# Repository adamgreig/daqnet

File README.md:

# DAQnet

Experiment into FPGAs for distributed data acquisition.

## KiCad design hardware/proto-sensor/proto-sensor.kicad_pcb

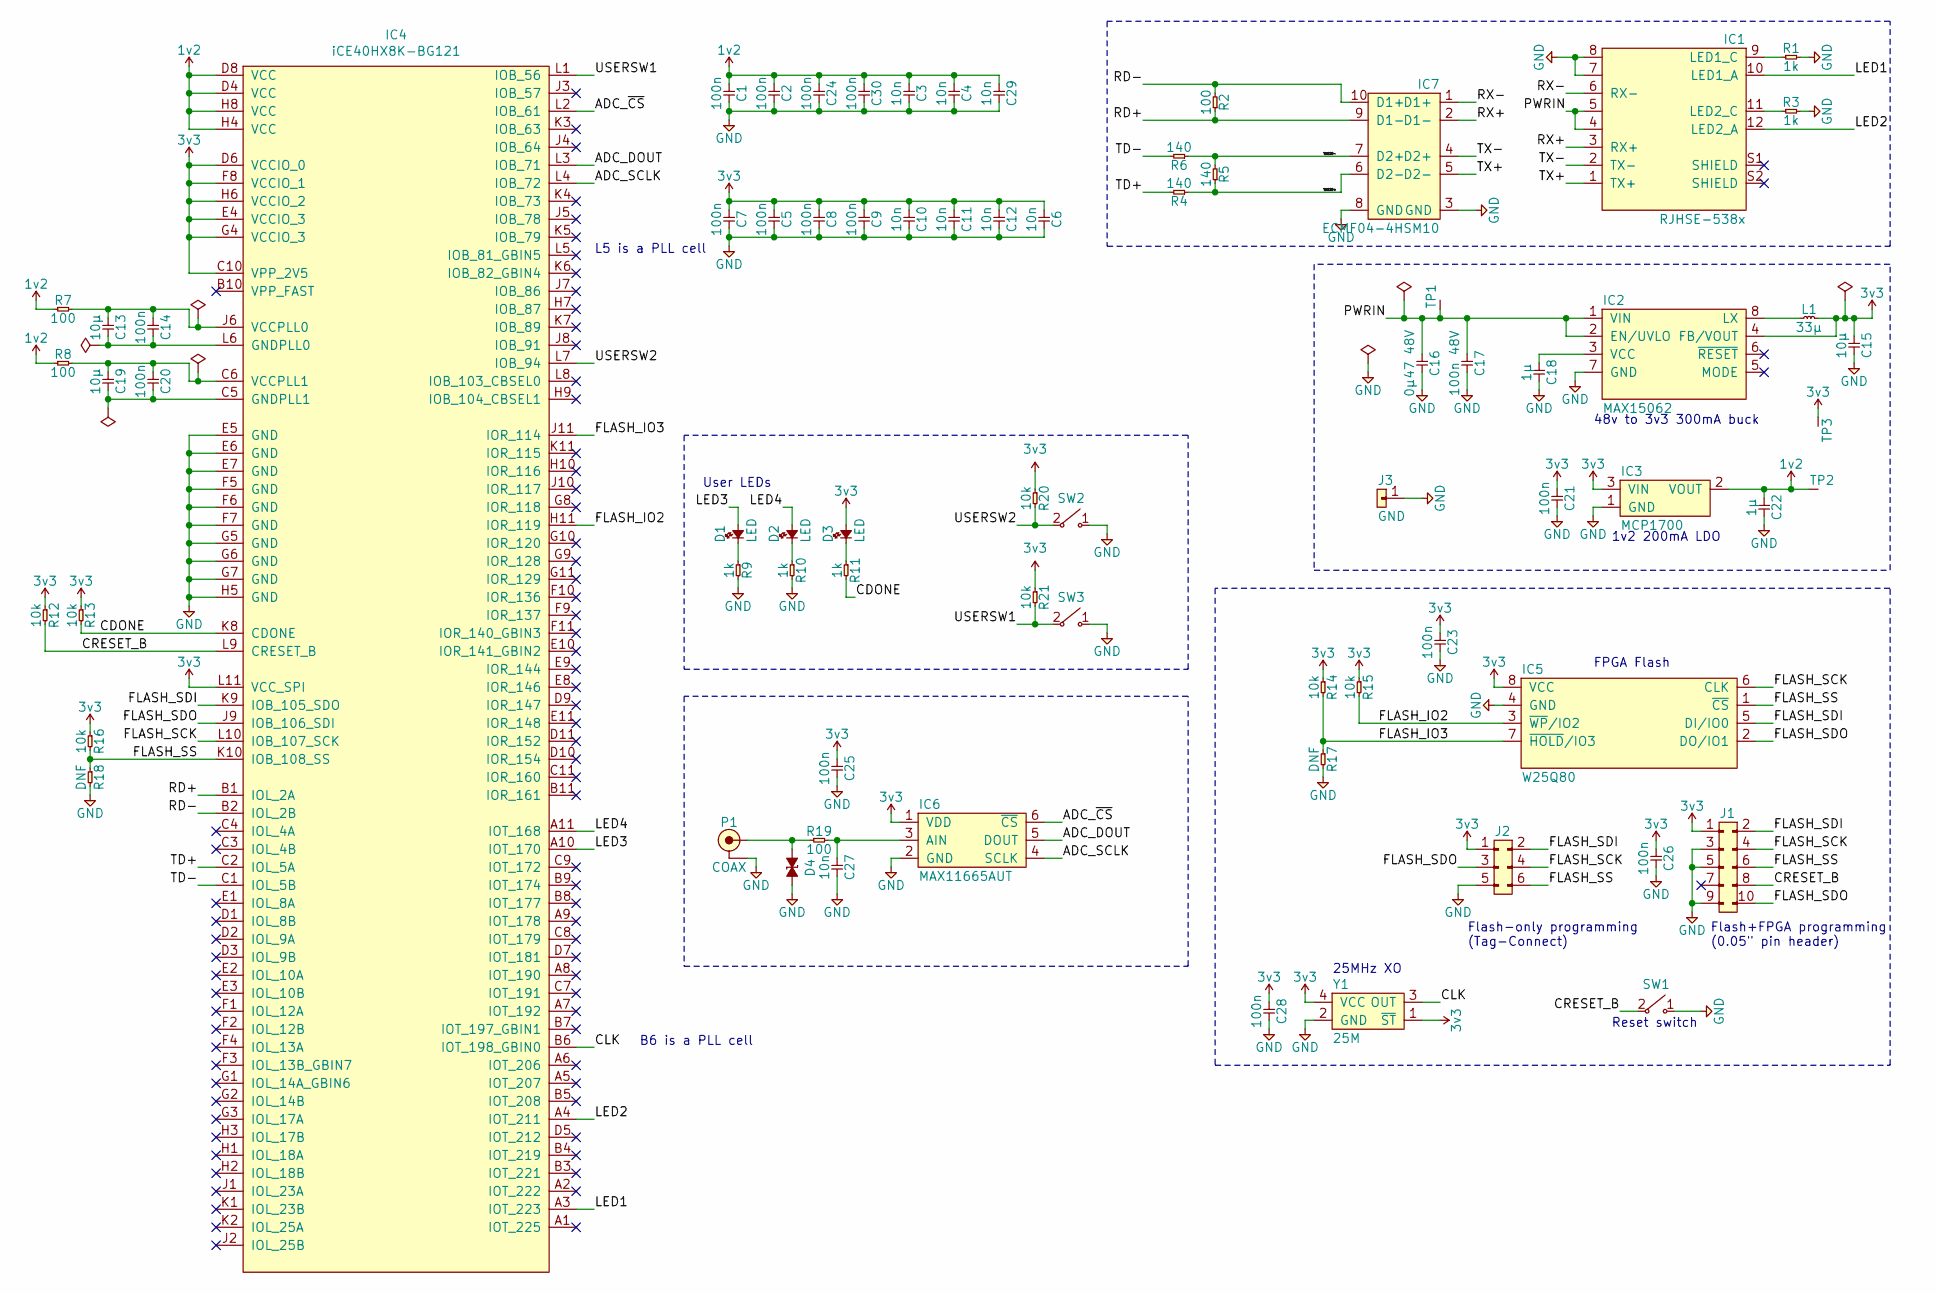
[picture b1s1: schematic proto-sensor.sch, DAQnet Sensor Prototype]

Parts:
C1, C2, C5, C7, C8, C9, C14, C20, C21, C23, C24, C25, C26, C28, C30: 100n; 0402; Voltage Rating 16; Farnell 2810260
C3, C4, C6, C10, C11, C12, C27, C29: 10n; 0402; Voltage Rating 50; Farnell 2470416
C13, C15, C19: 10µ; 0603; Voltage Rating 6.3; Farnell 2611921
C16: 0µ47 48V; 0603; Voltage Rating 50; Farnell 2211183
C17: 100n 48V; 0603; Voltage Rating 50; Farnell 431989
C18, C22: 1µ; 0402; Voltage Rating 10; Farnell 1458896
D1, D2: LED; 0603-LED; Farnell 2290328
D3: LED; 0603-LED; Farnell 2290329
D4: ESD_DIODE; 0402; Farnell 2368169
IC1: RJHSE-538x; RJHSE-538X; Farnell 1462758
IC2: MAX15062; TDFN-8; Farnell 2516650
IC3: MCP1700; SOT-23; Farnell 1851940
IC4: iCE40HX8K-BG121; Lattice-BG121; DigiKey 220-2148-ND
IC5: W25Q80; UFDFN-8; DigiKey W25Q80DVUXIECT-ND
IC6: MAX11665AUT; SOT-23-6; Farnell 2513633
IC7: ECMF04-4HSM10; uQFN-10L; Farnell 2462664
J1: FTSH-105-01-F-D-K; Farnell 2856426
J2: TC2030-NL
J3: GND; SIL-254P-01
L1: 33µ; LPS4018; Farnell 2408110
P1: COAX; BNC_PCB_RA_5-1634556-0; Farnell 1248952
R1, R3, R9, R10, R11: 1k; 0402; Voltage Rating 50; Farnell 2331474
R2, R7, R8, R19: 100; 0402; Voltage Rating 50; Farnell 9239111
R4, R5, R6: 140; 0402; Voltage Rating 50; Farnell 2302541
R12, R13, R14, R15, R16, R20, R21: 10k; 0402; Voltage Rating 50; Farnell 2302739
R17, R18: DNF; 0402
SW1, SW2, SW3: KSR232G; Farnell 2845744
TP1, TP2, TP3: TESTPAD
Y1: 25M; XTAL-25x20; Farnell 2849479

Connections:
1v2: C1.1, C2.1, C3.1, C4.1, C22.1, C24.1, C29.1, C30.1, IC3.2 (VOUT), IC4.D4 (VCC), IC4.D8 (VCC), IC4.H4 (VCC), IC4.H8 (VCC), R7.1, R8.1, TP2.1
3v3: C5.1, C6.1, C7.1, C8.1, C9.1, C10.1, C11.1, C12.1, C15.1, C21.1, C23.1, C25.1, C26.1, C28.1, D3.2, IC2.4 (FB/VOUT), IC3.3 (VIN), IC4.C10 (VPP_2V5), IC4.D6 (VCCIO_0), IC4.E4 (VCCIO_3), IC4.F8 (VCCIO_1), IC4.G4 (VCCIO_3), IC4.H6 (VCCIO_2), IC4.L11 (VCC_SPI), IC5.8 (VCC), IC6.1 (VDD), J1.1, J2.1, L1.2, R12.1, R13.1, R14.1, R15.1, R16.1, R20.1, R21.1, TP3.1, Y1.1 (~ST), Y1.4 (VCC)
/ADC_DOUT: IC4.L3 (IOB_71), IC6.5 (DOUT)
/ADC_SCLK: IC4.L4 (IOB_72), IC6.4 (SCLK)
/ADC_~CS: IC4.L2 (IOB_61), IC6.6 (~CS)
/CDONE: IC4.K8 (CDONE), R11.2, R13.2
/CLK: IC4.B6 (IOT_198_GBIN0), Y1.3 (OUT)
/CRESET_B: IC4.L9 (CRESET_B), J1.8, R12.2, SW1.2
/FLASH_IO2: IC4.H11 (IOR_119), IC5.3 (~WP~/IO2), R15.2
/FLASH_IO3: IC4.J11 (IOR_114), IC5.7 (~HOLD~/IO3), R14.2, R17.1
/FLASH_SCK: IC4.L10 (IOB_107_SCK), IC5.6 (CLK), J1.4, J2.4
/FLASH_SDI: IC4.K9 (IOB_105_SDO), IC5.5 (DI/IO0), J1.2, J2.2
/FLASH_SDO: IC4.J9 (IOB_106_SDI), IC5.2 (DO/IO1), J1.10, J2.3
/FLASH_SS: IC4.K10 (IOB_108_SS), IC5.1 (~CS), J1.6, J2.6, R16.2, R18.1
/LED1: IC1.10 (LED1_A), IC4.A3 (IOT_223)
/LED2: IC1.12 (LED2_A), IC4.A4 (IOT_211)
/LED3: D1.2, IC4.A10 (IOT_170)
/LED4: D2.2, IC4.A11 (IOT_168)
/PWRIN: C16.1, C17.1, IC1.4, IC1.5, IC2.1 (VIN), IC2.2 (EN/UVLO), TP1.1
/RD+: IC4.B1 (IOL_2A), IC7.9 (D1-), R2.1
/RD-: IC4.B2 (IOL_2B), IC7.10 (D1+), R2.2
/RX+: IC1.3 (RX+), IC7.2 (D1-)
/RX-: IC1.6 (RX-), IC7.1 (D1+)
/TD+: IC4.C2 (IOL_5A), R4.2
/TD-: IC4.C1 (IOL_5B), R6.2
/TDESD+: IC7.6 (D2-), R4.1, R5.1
/TDESD-: IC7.7 (D2+), R5.2, R6.1
/TX+: IC1.1 (TX+), IC7.5 (D2-)
/TX-: IC1.2 (TX-), IC7.4 (D2+)
/USERSW1: IC4.L1 (IOB_56), R21.2, SW3.2
/USERSW2: IC4.L7 (IOB_94), R20.2, SW2.2
GND: C1.2, C2.2, C3.2, C4.2, C5.2, C6.2, C7.2, C8.2, C9.2, C10.2, C11.2, C12.2, C15.2, C16.2, C17.2, C18.2, C21.2, C22.2, C23.2, C24.2, C25.2, C26.2, C27.2, C28.2, C29.2, C30.2, D4.2, IC1.7, IC1.8, IC2.7 (GND), IC3.1 (GND), IC4.E5 (GND), IC4.E6 (GND), IC4.E7 (GND), IC4.F5 (GND), IC4.F6 (GND), IC4.F7 (GND), IC4.G5 (GND), IC4.G6 (GND), IC4.G7 (GND), IC4.H5 (GND), IC5.4 (GND), IC6.2 (GND), IC7.3 (GND), IC7.8 (GND), J1.3, J1.5, J1.9, J2.5, J3.1, P1.2 (GND), R1.2, R3.2, R9.2, R10.2, R17.2, R18.2, SW1.1, SW2.1, SW3.1, Y1.2 (GND)
unnamed: C13.1, C14.1, IC4.J6 (VCCPLL0), R7.2
unnamed: C13.2, C14.2, IC4.L6 (GNDPLL0)
unnamed: C18.1, IC2.3 (VCC)
unnamed: C19.1, C20.1, IC4.C6 (VCCPLL1), R8.2
unnamed: C19.2, C20.2, IC4.C5 (GNDPLL1)
unnamed: C27.1, IC6.3 (AIN), R19.2
unnamed: D1.1, R9.1
unnamed: D2.1, R10.1
unnamed: D3.1, R11.1
unnamed: D4.1, P1.1 (RF), R19.1
unnamed: IC1.9 (LED1_C), R1.1
unnamed: IC1.11 (LED2_C), R3.1
unnamed: IC2.8 (LX), L1.1

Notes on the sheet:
Flash-only programming (Tag-Connect)
Flash+FPGA programming (0.05" pin header)
FPGA Flash
48v to 3v3 300mA buck
25MHz XO
Reset switch
User LEDs
1v2 200mA LDO
L5 is a PLL cell
B6 is a PLL cell

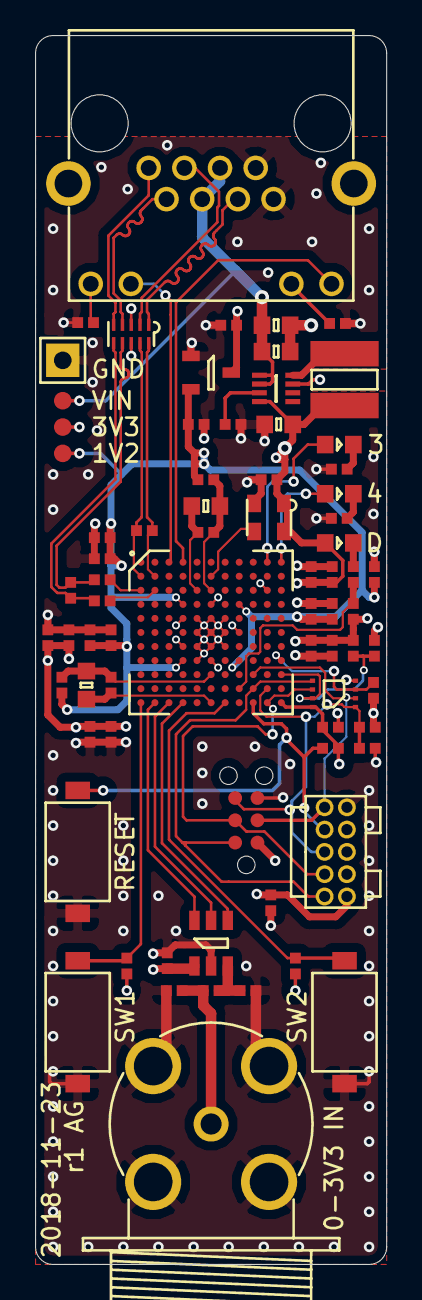
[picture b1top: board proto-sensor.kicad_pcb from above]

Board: 4 copper layers, 20.0 x 70.0 mm, 74 parts (0 on the bottom side), 45 nets.

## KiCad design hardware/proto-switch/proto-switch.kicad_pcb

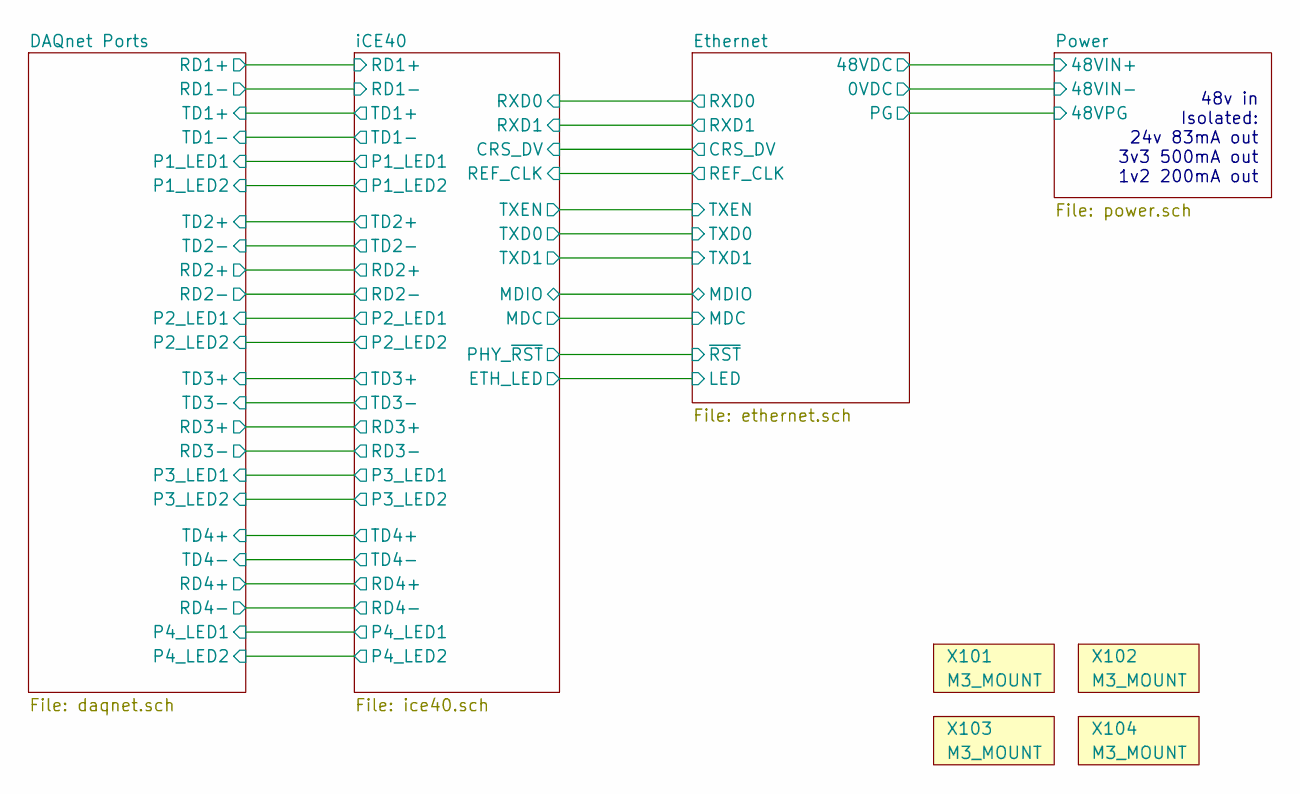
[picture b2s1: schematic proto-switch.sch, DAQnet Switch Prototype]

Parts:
X101, X102, X103, X104: M3_MOUNT

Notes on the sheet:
48v in Isolated: 24v 83mA out 3v3 500mA out 1v2 200mA out

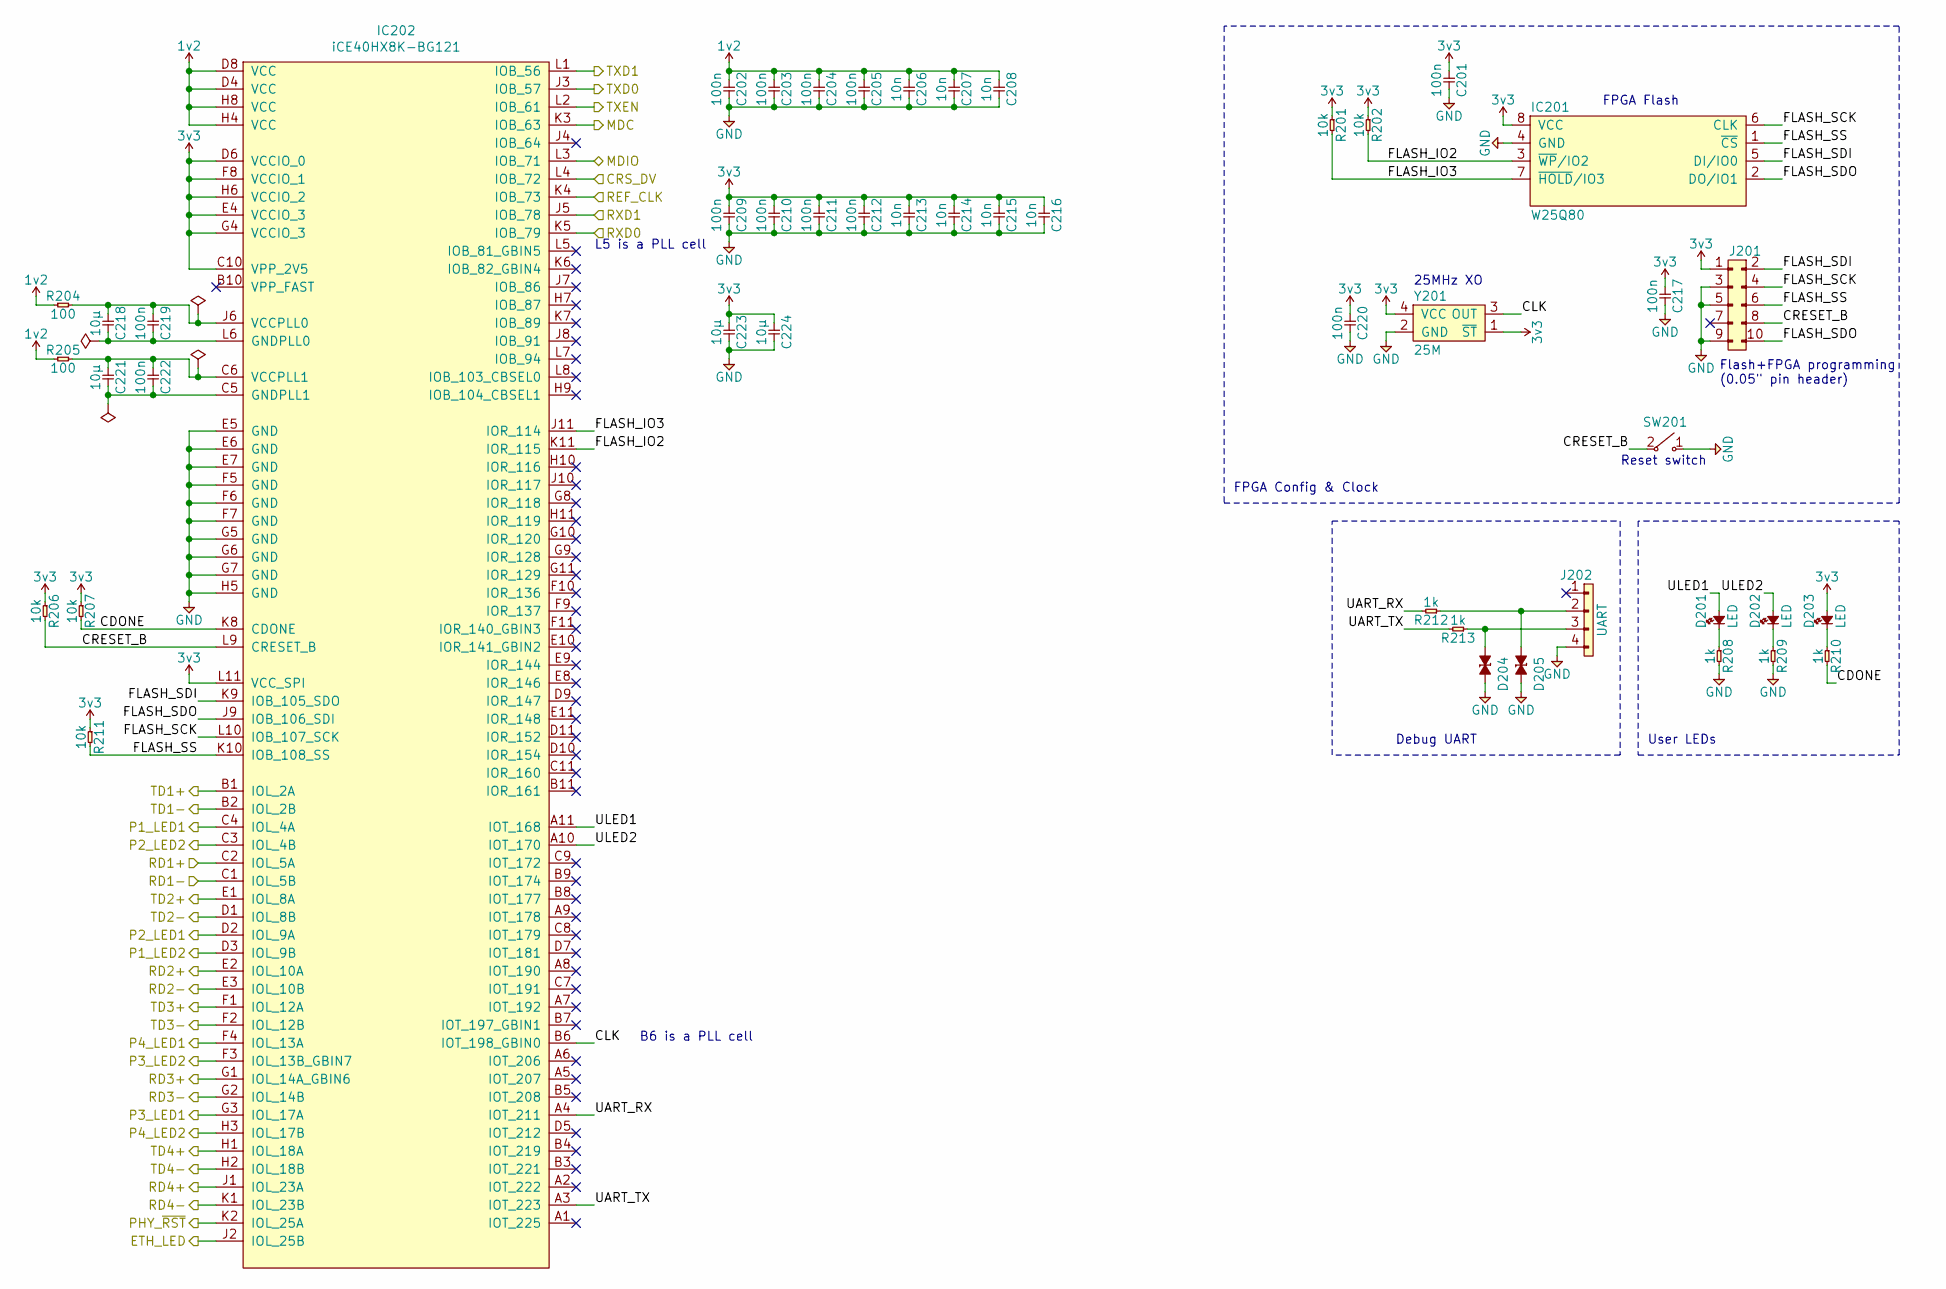
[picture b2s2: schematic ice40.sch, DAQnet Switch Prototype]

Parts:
C201, C202, C203, C204, C205, C209, C210, C211, C212, C217, C219, C220, C222: 100n; 0402; Voltage 16; Farnell 2810260
C206, C207, C208, C213, C214, C215, C216: 10n; 0402; Voltage 50; Farnell 2470416
C218, C221, C223, C224: 10µ; 0603; Voltage 6.3; Farnell 2611921
D201, D202: LED; 0603-LED; Farnell 2290328
D203: LED; 0603-LED; Farnell 2290329
D204, D205: ESD_DIODE; 0402; Farnell 2368169
IC201: W25Q80; UFDFN-8; DigiKey W25Q80DVUXIECT-ND
IC202: iCE40HX8K-BG121; Lattice-BG121; DigiKey 220-2148-ND
J201: FTSH-105-01-F-D-K; Farnell 2856426
J202: UART; SM04B-PASS
R201, R202, R206, R207, R211: 10k; 0402; Voltage 50; Farnell 2302739
R204, R205: 100; 0402; Voltage 50; Farnell 9239111
R208, R209, R210, R212, R213: 1k; 0402; Voltage 50; Farnell 2331474
SW201: KSR232G; Farnell 2845744
Y201: 25M; XTAL-25x20; Farnell 2849479

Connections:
1v2: C202.1, C203.1, C204.1, C205.1, C206.1, C207.1, C208.1, IC202.D4 (VCC), IC202.D8 (VCC), IC202.H4 (VCC), IC202.H8 (VCC), R204.1, R205.1; also elsewhere on the board
3v3: C201.1, C209.1, C210.1, C211.1, C212.1, C213.1, C214.1, C215.1, C216.1, C217.1, C220.1, C223.1, C224.1, D203.2, IC201.8 (VCC), IC202.C10 (VPP_2V5), IC202.D6 (VCCIO_0), IC202.E4 (VCCIO_3), IC202.F8 (VCCIO_1), IC202.G4 (VCCIO_3), IC202.H6 (VCCIO_2), IC202.L11 (VCC_SPI), J201.1, R201.1, R202.1, R206.1, R207.1, R211.1, Y201.1 (~ST), Y201.4 (VCC); also elsewhere on the board
/DAQnet Ports/P1_LED1: IC202.C4 (IOL_4A); also elsewhere on the board
/DAQnet Ports/P1_LED2: IC202.D3 (IOL_9B); also elsewhere on the board
/DAQnet Ports/P2_LED1: IC202.D2 (IOL_9A); also elsewhere on the board
/DAQnet Ports/P2_LED2: IC202.C3 (IOL_4B); also elsewhere on the board
/DAQnet Ports/P3_LED1: IC202.G3 (IOL_17A); also elsewhere on the board
/DAQnet Ports/P3_LED2: IC202.F3 (IOL_13B_GBIN7); also elsewhere on the board
/DAQnet Ports/P4_LED1: IC202.F4 (IOL_13A); also elsewhere on the board
/DAQnet Ports/P4_LED2: IC202.H3 (IOL_17B); also elsewhere on the board
/DAQnet Ports/RD1+: IC202.C2 (IOL_5A); also elsewhere on the board
/DAQnet Ports/RD1-: IC202.C1 (IOL_5B); also elsewhere on the board
/DAQnet Ports/RD2+: IC202.E2 (IOL_10A); also elsewhere on the board
/DAQnet Ports/RD2-: IC202.E3 (IOL_10B); also elsewhere on the board
/DAQnet Ports/RD3+: IC202.G1 (IOL_14A_GBIN6); also elsewhere on the board
/DAQnet Ports/RD3-: IC202.G2 (IOL_14B); also elsewhere on the board
/DAQnet Ports/RD4+: IC202.J1 (IOL_23A); also elsewhere on the board
/DAQnet Ports/RD4-: IC202.K1 (IOL_23B); also elsewhere on the board
/DAQnet Ports/TD1+: IC202.B1 (IOL_2A); also elsewhere on the board
/DAQnet Ports/TD1-: IC202.B2 (IOL_2B); also elsewhere on the board
/DAQnet Ports/TD2+: IC202.E1 (IOL_8A); also elsewhere on the board
/DAQnet Ports/TD2-: IC202.D1 (IOL_8B); also elsewhere on the board
/DAQnet Ports/TD3+: IC202.F1 (IOL_12A); also elsewhere on the board
/DAQnet Ports/TD3-: IC202.F2 (IOL_12B); also elsewhere on the board
/DAQnet Ports/TD4+: IC202.H1 (IOL_18A); also elsewhere on the board
/DAQnet Ports/TD4-: IC202.H2 (IOL_18B); also elsewhere on the board
/Ethernet/CRS_DV: IC202.L4 (IOB_72); also elsewhere on the board
/Ethernet/MDC: IC202.K3 (IOB_63); also elsewhere on the board
/Ethernet/MDIO: IC202.L3 (IOB_71); also elsewhere on the board
/Ethernet/REF_CLK: IC202.K4 (IOB_73); also elsewhere on the board
/Ethernet/RXD0: IC202.K5 (IOB_79); also elsewhere on the board
/Ethernet/RXD1: IC202.J5 (IOB_78); also elsewhere on the board
/Ethernet/TXD0: IC202.J3 (IOB_57); also elsewhere on the board
/Ethernet/TXD1: IC202.L1 (IOB_56); also elsewhere on the board
/Ethernet/TXEN: IC202.L2 (IOB_61); also elsewhere on the board
/iCE40/CDONE: IC202.K8 (CDONE), R207.2, R210.2
/iCE40/CLK: IC202.B6 (IOT_198_GBIN0), Y201.3 (OUT)
/iCE40/CRESET_B: IC202.L9 (CRESET_B), J201.8, R206.2, SW201.2
/iCE40/ETH_LED: IC202.J2 (IOL_25B); also elsewhere on the board
/iCE40/FLASH_IO2: IC201.3 (~WP~/IO2), IC202.K11 (IOR_115), R202.2
/iCE40/FLASH_IO3: IC201.7 (~HOLD~/IO3), IC202.J11 (IOR_114), R201.2
/iCE40/FLASH_SCK: IC201.6 (CLK), IC202.L10 (IOB_107_SCK), J201.4
/iCE40/FLASH_SDI: IC201.5 (DI/IO0), IC202.K9 (IOB_105_SDO), J201.2
/iCE40/FLASH_SDO: IC201.2 (DO/IO1), IC202.J9 (IOB_106_SDI), J201.10
/iCE40/FLASH_SS: IC201.1 (~CS), IC202.K10 (IOB_108_SS), J201.6, R211.2
/iCE40/PHY_~RST: IC202.K2 (IOL_25A); also elsewhere on the board
/iCE40/UART_RX: IC202.A4 (IOT_211), R212.2
/iCE40/UART_TX: IC202.A3 (IOT_223), R213.2
/iCE40/ULED1: D201.2, IC202.A11 (IOT_168)
/iCE40/ULED2: D202.2, IC202.A10 (IOT_170)
GND: C201.2, C202.2, C203.2, C204.2, C205.2, C206.2, C207.2, C208.2, C209.2, C210.2, C211.2, C212.2, C213.2, C214.2, C215.2, C216.2, C217.2, C220.2, C223.2, C224.2, D204.2, D205.2, IC201.4 (GND), IC202.E5 (GND), IC202.E6 (GND), IC202.E7 (GND), IC202.F5 (GND), IC202.F6 (GND), IC202.F7 (GND), IC202.G5 (GND), IC202.G6 (GND), IC202.G7 (GND), IC202.H5 (GND), J201.3, J201.5, J201.9, J202.4, R208.2, R209.2, SW201.1, Y201.2 (GND); also elsewhere on the board
unnamed: C218.1, C219.1, IC202.J6 (VCCPLL0), R204.2
unnamed: C218.2, C219.2, IC202.L6 (GNDPLL0)
unnamed: C221.1, C222.1, IC202.C6 (VCCPLL1), R205.2
unnamed: C221.2, C222.2, IC202.C5 (GNDPLL1)
unnamed: D201.1, R208.1
unnamed: D202.1, R209.1
unnamed: D203.1, R210.1
unnamed: D204.1, J202.3, R213.1
unnamed: D205.1, J202.2, R212.1

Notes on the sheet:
User LEDs
L5 is a PLL cell
B6 is a PLL cell
Flash+FPGA programming (0.05" pin header)
FPGA Flash
25MHz XO
Reset switch
Debug UART
FPGA Config & Clock

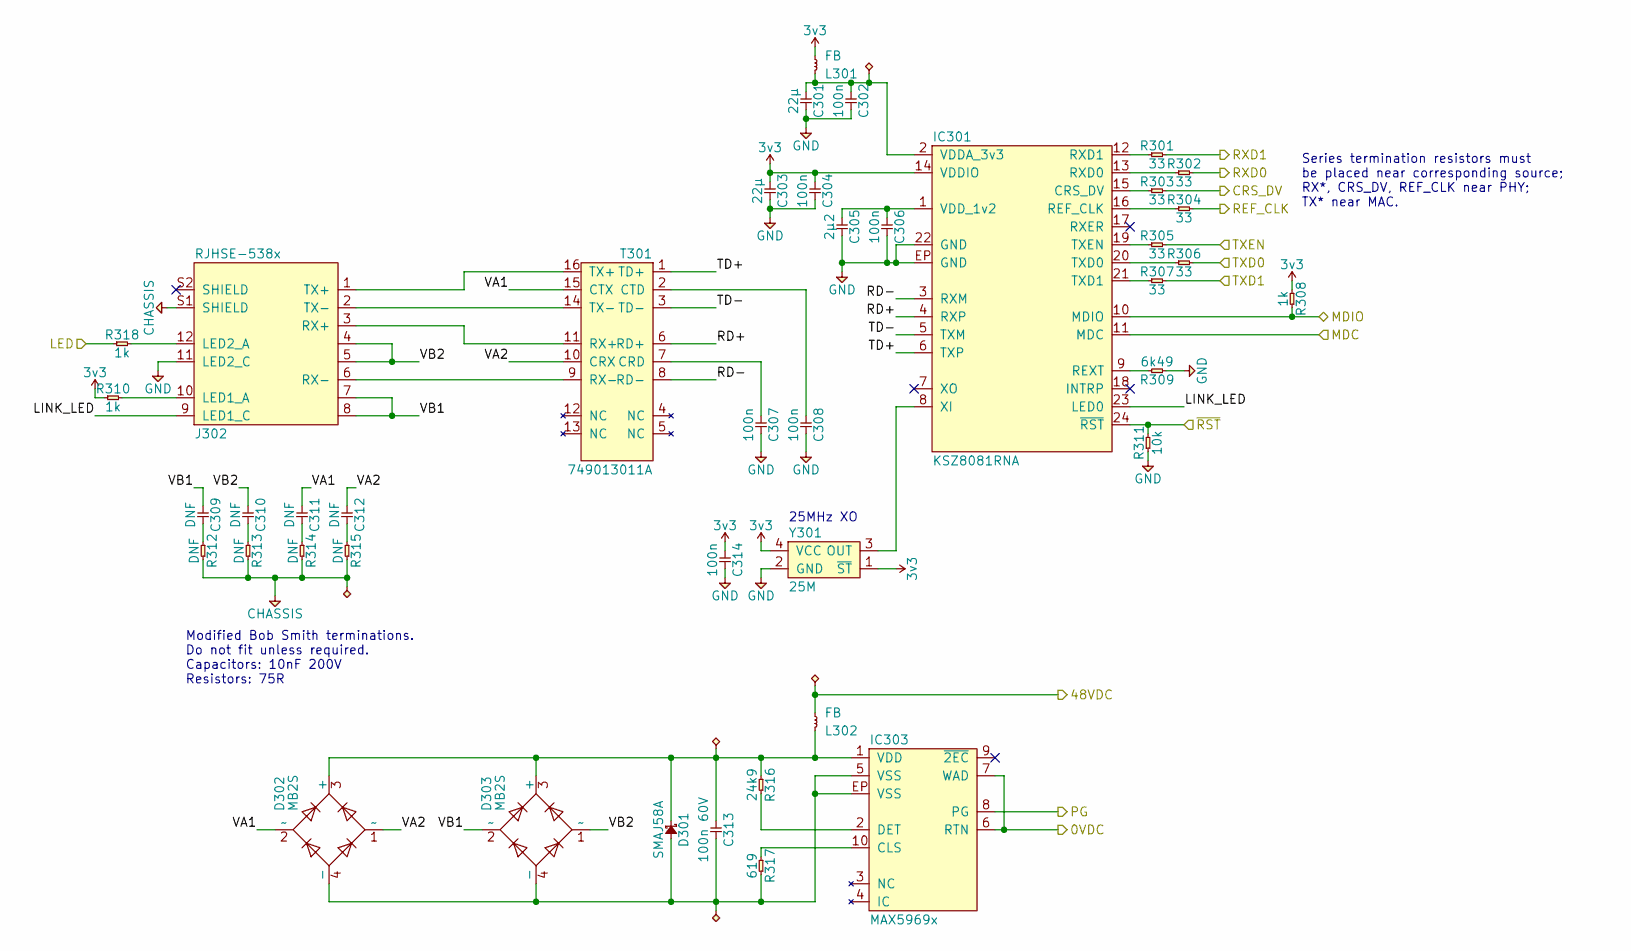
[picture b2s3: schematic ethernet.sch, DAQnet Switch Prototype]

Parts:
C301, C303: 22µ; 1206; Voltage 16; Farnell 2320923
C302, C304, C306, C314: 100n; 0402; Voltage 16; Farnell 2810260
C305: 2µ2; 0603; Voltage 10; Farnell 2320817
C307, C308: 100n; 0603; Voltage 50; Farnell 431989
C309, C310, C311, C312: DNF; 0805
C313: 100n 60V; 0805; Farnell 2496941
D301: SMAJ58A; DO-214AC-SMA; Farnell 1899460
D302, D303: MB2S; TO-269AA; Farnell 9550003
IC301: KSZ8081RNA; QFN-24-EP-MICREL; Farnell 2509802
IC303: MAX5969x; DFN-10-EP-MAX; Farnell 2514586
J302: RJHSE-538x; RJHSE-538X; Farnell 1462758
L301, L302: FB; 0603; Farnell 1463451
R301, R302, R303, R304, R305, R306, R307: 33; 0402; Voltage 50; Farnell 2302472
R308, R310, R318: 1k; 0402; Voltage 50; Farnell 2331474
R309: 6k49; 0402; Voltage 50; Farnell 2302722
R311: 10k; 0402; Voltage 50; Farnell 2302739
R312, R313, R314, R315: DNF; 0603
R316: 24k9; 0402; Voltage 50; Farnell 1469699
R317: 619; 0402; Voltage 50; Farnell 2302613
T301: 749013011A; 749010012A; Farnell 2422553
Y301: 25M; XTAL-25x20; Farnell 2849479

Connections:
3v3: C303.1, C304.1, C314.1, IC301.14 (VDDIO), L301.1, R308.1, R310.1, Y301.1 (~ST), Y301.4 (VCC); also elsewhere on the board
/Ethernet/0VDC: IC303.6 (RTN), IC303.7 (WAD); also elsewhere on the board
/Ethernet/48VDC: L302.1; also elsewhere on the board
/Ethernet/CRS_DV: R303.2; also elsewhere on the board
/Ethernet/LINK_LED: IC301.23 (LED0), J302.9 (LED1_C)
/Ethernet/MDC: IC301.11 (MDC); also elsewhere on the board
/Ethernet/MDIO: IC301.10 (MDIO), R308.2; also elsewhere on the board
/Ethernet/RD+: IC301.4 (RXP), T301.6 (RD+)
/Ethernet/RD-: IC301.3 (RXM), T301.8 (RD-)
/Ethernet/REF_CLK: R304.2; also elsewhere on the board
/Ethernet/RXD0: R302.2; also elsewhere on the board
/Ethernet/RXD1: R301.2; also elsewhere on the board
/Ethernet/TD+: IC301.6 (TXP), T301.1 (TD+)
/Ethernet/TD-: IC301.5 (TXM), T301.3 (TD-)
/Ethernet/TXD0: R306.2; also elsewhere on the board
/Ethernet/TXD1: R307.2; also elsewhere on the board
/Ethernet/TXEN: R305.2; also elsewhere on the board
/Ethernet/VA1: C311.1, D302.2 (~~), T301.15 (CTX)
/Ethernet/VA2: C312.1, D302.1 (~~), T301.10 (CRX)
/Ethernet/VB1: C309.1, D303.2 (~~), J302.7, J302.8
/Ethernet/VB2: C310.1, D303.1 (~~), J302.4, J302.5
/Power/48VPG: IC303.8 (PG); also elsewhere on the board
/iCE40/ETH_LED: R318.1; also elsewhere on the board
/iCE40/PHY_~RST: IC301.24 (~RST), R311.2; also elsewhere on the board
CHASSIS: J302.S1 (SHIELD), R312.2, R313.2, R314.2, R315.2; also elsewhere on the board
GND: C301.2, C302.2, C303.2, C304.2, C305.2, C306.2, C307.2, C308.2, C314.2, IC301.22 (GND), IC301.EP (GND), J302.11 (LED2_C), R309.1, R311.1, Y301.2 (GND); also elsewhere on the board
unnamed: C301.1, C302.1, IC301.2 (VDDA_3v3), L301.2
unnamed: C305.1, C306.1, IC301.1 (VDD_1v2)
unnamed: C307.1, T301.7 (CRD)
unnamed: C308.1, T301.2 (CTD)
unnamed: C309.2, R312.1
unnamed: C310.2, R313.1
unnamed: C311.2, R314.1
unnamed: C312.2, R315.1
unnamed: C313.1, D301.1, D302.3 (+), D303.3 (+), IC303.1 (VDD), L302.2, R316.1
unnamed: C313.2, D301.2, D302.4 (-), D303.4 (-), IC303.5 (VSS), IC303.EP (VSS), R317.2
unnamed: IC301.8 (XI), Y301.3 (OUT)
unnamed: IC301.9 (REXT), R309.2
unnamed: IC301.12 (RXD1), R301.1
unnamed: IC301.13 (RXD0), R302.1
unnamed: IC301.15 (CRS_DV), R303.1
unnamed: IC301.16 (REF_CLK), R304.1
unnamed: IC301.19 (TXEN), R305.1
unnamed: IC301.20 (TXD0), R306.1
unnamed: IC301.21 (TXD1), R307.1
unnamed: IC303.2 (DET), R316.2
unnamed: IC303.10 (CLS), R317.1
unnamed: J302.1 (TX+), T301.16 (TX+)
unnamed: J302.2 (TX-), T301.14 (TX-)
unnamed: J302.3 (RX+), T301.11 (RX+)
unnamed: J302.6 (RX-), T301.9 (RX-)
unnamed: J302.10 (LED1_A), R310.2
unnamed: J302.12 (LED2_A), R318.2

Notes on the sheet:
Series termination resistors must be placed near corresponding source; RX*, CRS_DV, REF_CLK near PHY; TX* near MAC.
Modified Bob Smith terminations. Do not fit unless required. Capacitors: 10nF 200V Resistors: 75R
25MHz XO

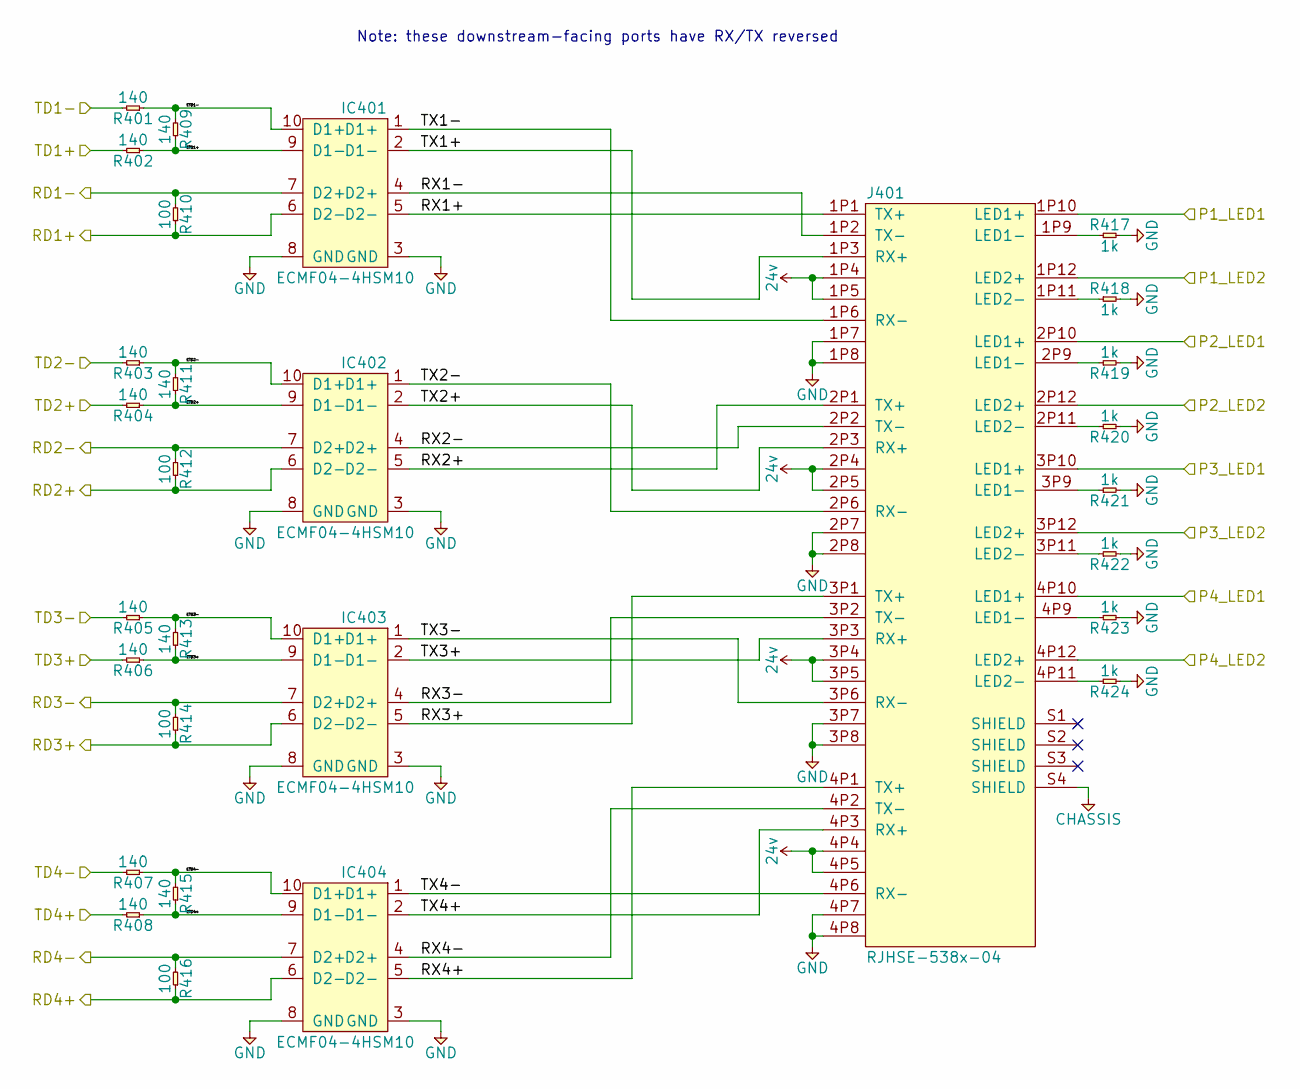
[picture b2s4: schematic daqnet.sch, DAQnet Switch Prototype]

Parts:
IC401, IC402, IC403, IC404: ECMF04-4HSM10; uQFN-10L; Farnell 2462664
J401: RJHSE-538x-04; RJHSE-538X-04; Farnell 1860606
R401, R402, R403, R404, R405, R406, R407, R408, R409, R411, R413, R415: 140; 0402; Voltage 50; Farnell 2302541
R410, R412, R414, R416: 100; 0402; Voltage 50; Farnell 9239111
R417, R418, R419, R420, R421, R422, R423, R424: 1k; 0402; Voltage 50; Farnell 2331474

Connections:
24v: J401.1P4, J401.1P5, J401.2P4, J401.2P5, J401.3P4, J401.3P5, J401.4P4, J401.4P5; also elsewhere on the board
/DAQnet Ports/ETD1+: IC401.9 (D1-), R402.1, R409.1
/DAQnet Ports/ETD1-: IC401.10 (D1+), R401.1, R409.2
/DAQnet Ports/ETD2+: IC402.9 (D1-), R404.1, R411.1
/DAQnet Ports/ETD2-: IC402.10 (D1+), R403.1, R411.2
/DAQnet Ports/ETD3+: IC403.9 (D1-), R406.1, R413.1
/DAQnet Ports/ETD3-: IC403.10 (D1+), R405.1, R413.2
/DAQnet Ports/ETD4+: IC404.9 (D1-), R408.1, R415.1
/DAQnet Ports/ETD4-: IC404.10 (D1+), R407.1, R415.2
/DAQnet Ports/P1_LED1: J401.1P10 (LED1+); also elsewhere on the board
/DAQnet Ports/P1_LED2: J401.1P12 (LED2+); also elsewhere on the board
/DAQnet Ports/P2_LED1: J401.2P10 (LED1+); also elsewhere on the board
/DAQnet Ports/P2_LED2: J401.2P12 (LED2+); also elsewhere on the board
/DAQnet Ports/P3_LED1: J401.3P10 (LED1+); also elsewhere on the board
/DAQnet Ports/P3_LED2: J401.3P12 (LED2+); also elsewhere on the board
/DAQnet Ports/P4_LED1: J401.4P10 (LED1+); also elsewhere on the board
/DAQnet Ports/P4_LED2: J401.4P12 (LED2+); also elsewhere on the board
/DAQnet Ports/RD1+: IC401.6 (D2-), R410.1; also elsewhere on the board
/DAQnet Ports/RD1-: IC401.7 (D2+), R410.2; also elsewhere on the board
/DAQnet Ports/RD2+: IC402.6 (D2-), R412.1; also elsewhere on the board
/DAQnet Ports/RD2-: IC402.7 (D2+), R412.2; also elsewhere on the board
/DAQnet Ports/RD3+: IC403.6 (D2-), R414.1; also elsewhere on the board
/DAQnet Ports/RD3-: IC403.7 (D2+), R414.2; also elsewhere on the board
/DAQnet Ports/RD4+: IC404.6 (D2-), R416.1; also elsewhere on the board
/DAQnet Ports/RD4-: IC404.7 (D2+), R416.2; also elsewhere on the board
/DAQnet Ports/RX1+: IC401.5 (D2-), J401.1P1 (TX+)
/DAQnet Ports/RX1-: IC401.4 (D2+), J401.1P2 (TX-)
/DAQnet Ports/RX2+: IC402.5 (D2-), J401.2P1 (TX+)
/DAQnet Ports/RX2-: IC402.4 (D2+), J401.2P2 (TX-)
/DAQnet Ports/RX3+: IC403.5 (D2-), J401.3P1 (TX+)
/DAQnet Ports/RX3-: IC403.4 (D2+), J401.3P2 (TX-)
/DAQnet Ports/RX4+: IC404.5 (D2-), J401.4P1 (TX+)
/DAQnet Ports/RX4-: IC404.4 (D2+), J401.4P2 (TX-)
/DAQnet Ports/TD1+: R402.2; also elsewhere on the board
/DAQnet Ports/TD1-: R401.2; also elsewhere on the board
/DAQnet Ports/TD2+: R404.2; also elsewhere on the board
/DAQnet Ports/TD2-: R403.2; also elsewhere on the board
/DAQnet Ports/TD3+: R406.2; also elsewhere on the board
/DAQnet Ports/TD3-: R405.2; also elsewhere on the board
/DAQnet Ports/TD4+: R408.2; also elsewhere on the board
/DAQnet Ports/TD4-: R407.2; also elsewhere on the board
/DAQnet Ports/TX1+: IC401.2 (D1-), J401.1P3 (RX+)
/DAQnet Ports/TX1-: IC401.1 (D1+), J401.1P6 (RX-)
/DAQnet Ports/TX2+: IC402.2 (D1-), J401.2P3 (RX+)
/DAQnet Ports/TX2-: IC402.1 (D1+), J401.2P6 (RX-)
/DAQnet Ports/TX3+: IC403.2 (D1-), J401.3P3 (RX+)
/DAQnet Ports/TX3-: IC403.1 (D1+), J401.3P6 (RX-)
/DAQnet Ports/TX4+: IC404.2 (D1-), J401.4P3 (RX+)
/DAQnet Ports/TX4-: IC404.1 (D1+), J401.4P6 (RX-)
CHASSIS: J401.S4 (SHIELD); also elsewhere on the board
GND: IC401.3 (GND), IC401.8 (GND), IC402.3 (GND), IC402.8 (GND), IC403.3 (GND), IC403.8 (GND), IC404.3 (GND), IC404.8 (GND), J401.1P7, J401.1P8, J401.2P7, J401.2P8, J401.3P7, J401.3P8, J401.4P7, J401.4P8, R417.2, R418.2, R419.2, R420.2, R421.2, R422.2, R423.2, R424.2; also elsewhere on the board
unnamed: J401.1P9 (LED1-), R417.1
unnamed: J401.1P11 (LED2-), R418.1
unnamed: J401.2P9 (LED1-), R419.1
unnamed: J401.2P11 (LED2-), R420.1
unnamed: J401.3P9 (LED1-), R421.1
unnamed: J401.3P11 (LED2-), R422.1
unnamed: J401.4P9 (LED1-), R423.1
unnamed: J401.4P11 (LED2-), R424.1

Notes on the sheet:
Note: these downstream-facing ports have RX/TX reversed

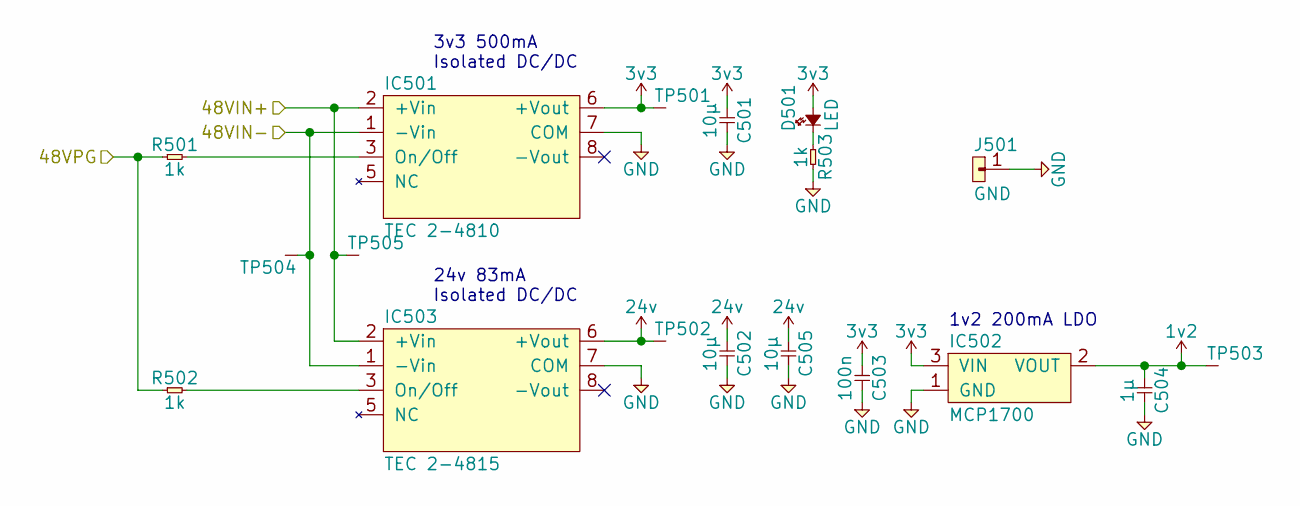
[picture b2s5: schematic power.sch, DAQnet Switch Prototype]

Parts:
C501: 10µ; 0603; Voltage 6.3; Farnell 2611921
C502, C505: 10µ; 0603; Voltage 25; Farnell 2469398
C503: 100n; 0402; Voltage 16; Farnell 2810260
C504: 1µ; 0402; Voltage 10; Farnell 1458896
D501: LED; 0603-LED; Farnell 2290328
IC501: TEC 2-4810; SIP-8-DCDC; Farnell 2854900
IC502: MCP1700; SOT-23; Farnell 1851940
IC503: TEC 2-4815; SIP-8-DCDC; Farnell 2854905
J501: GND; SIL-254P-01
R501, R502, R503: 1k; 0402; Voltage 50; Farnell 2331474
TP501, TP502, TP503, TP504, TP505: TESTPAD

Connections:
1v2: C504.1, IC502.2 (VOUT), TP503.1; also elsewhere on the board
3v3: C501.1, C503.1, D501.2, IC501.6 (+Vout), IC502.3 (VIN), TP501.1; also elsewhere on the board
24v: C502.1, C505.1, IC503.6 (+Vout), TP502.1; also elsewhere on the board
/Ethernet/0VDC: IC501.1 (-Vin), IC503.1 (-Vin), TP504.1; also elsewhere on the board
/Ethernet/48VDC: IC501.2 (+Vin), IC503.2 (+Vin), TP505.1; also elsewhere on the board
/Power/48VPG: R501.1, R502.1; also elsewhere on the board
GND: C501.2, C502.2, C503.2, C504.2, C505.2, IC501.7 (COM), IC502.1 (GND), IC503.7 (COM), J501.1, R503.2; also elsewhere on the board
unnamed: D501.1, R503.1
unnamed: IC501.3 (On/Off), R501.2
unnamed: IC503.3 (On/Off), R502.2

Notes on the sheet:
1v2 200mA LDO
3v3 500mA Isolated DC/DC
24v 83mA Isolated DC/DC

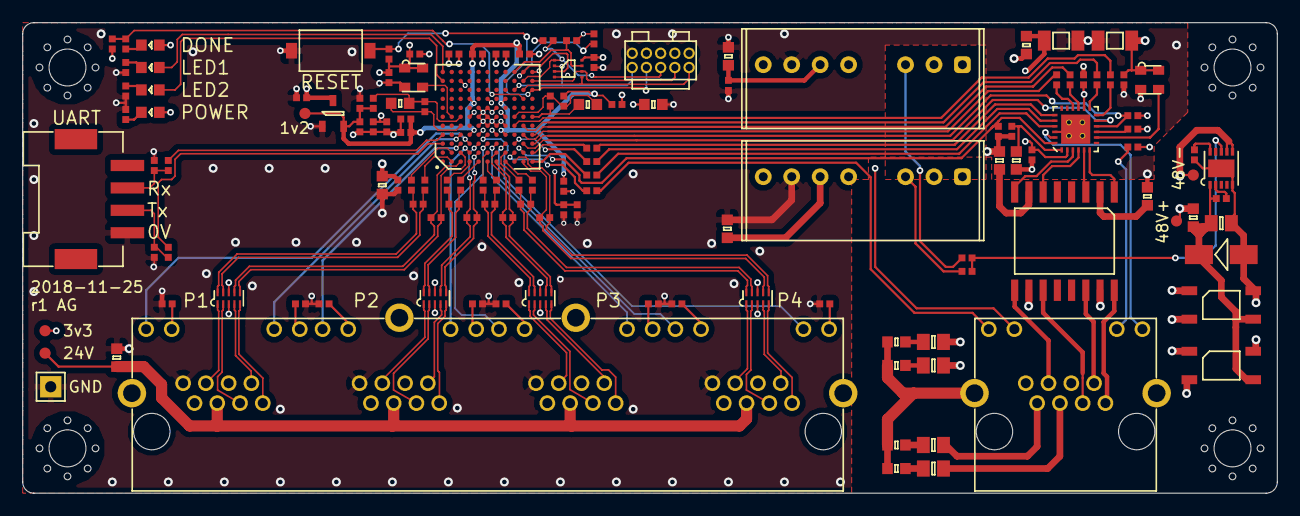
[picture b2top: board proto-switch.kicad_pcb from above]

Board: 4 copper layers, 112.0 x 42.0 mm, 140 parts (0 on the bottom side), 136 nets.

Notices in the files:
gateware/daqnet/platform.py:
Copyright 2019 Adam Greig
Released under the MIT license; see LICENSE for details.
